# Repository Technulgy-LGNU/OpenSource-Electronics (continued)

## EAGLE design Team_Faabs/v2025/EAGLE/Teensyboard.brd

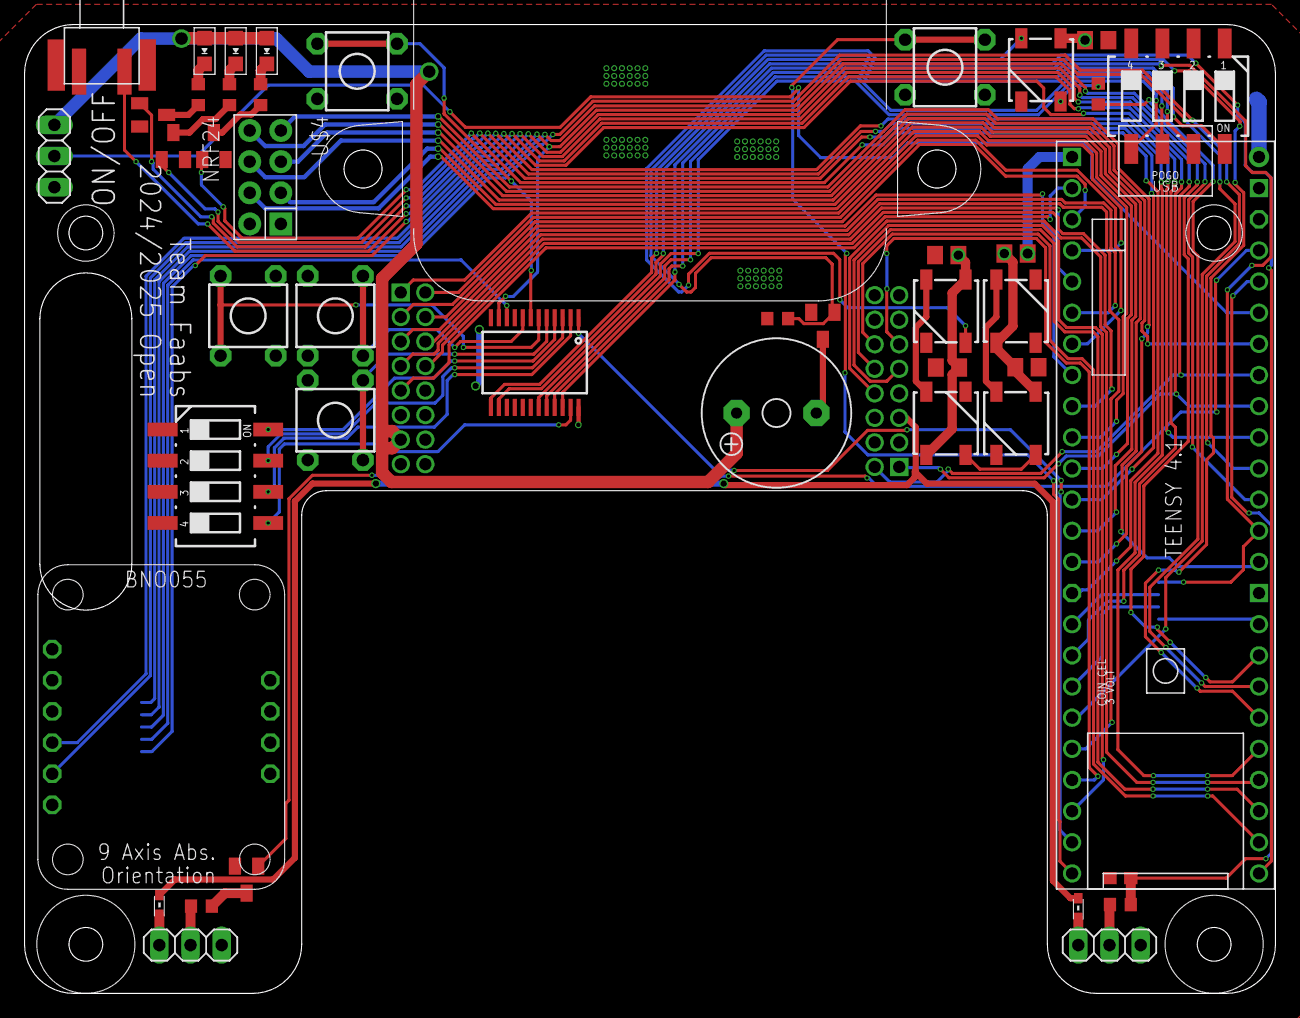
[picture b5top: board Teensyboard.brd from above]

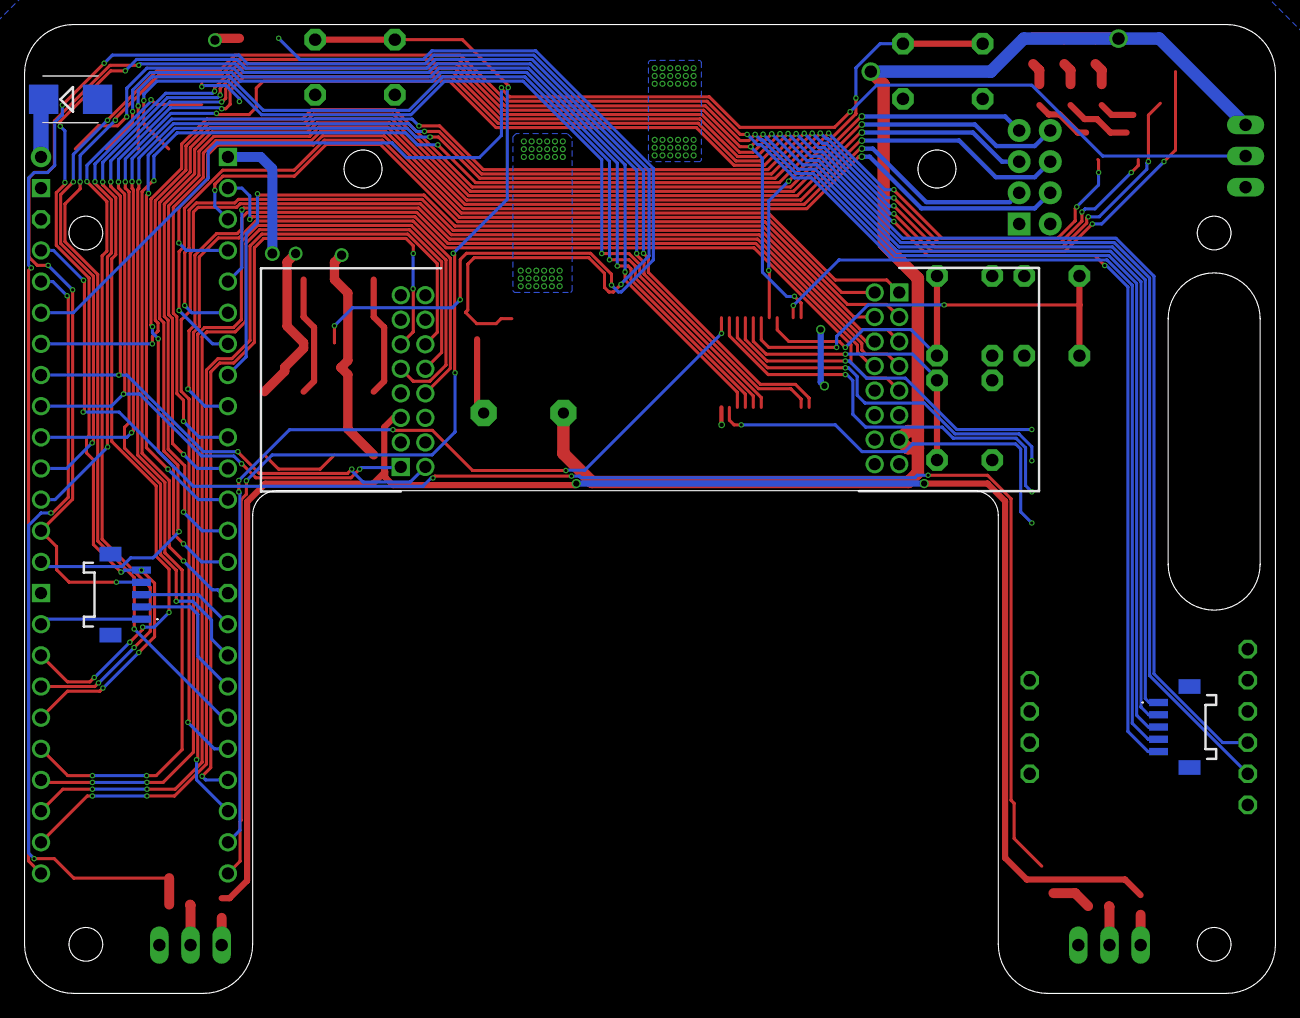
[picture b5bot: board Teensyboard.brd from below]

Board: 2 copper layers, 102.0 x 79.0 mm, 49 parts (5 on the bottom side), 77 nets.

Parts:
C1, C2, C3, C4, C5: 100n; C0805
C6: 1n; C0603
D1: SMB
D6, D7, D8, D9, D10: SPARKFUN-LED_WS2812B
J1, J5: TEENSY_CON_RIGHTANGLED; 208659-1640_SHDRRA16W55P200_2X8_1800X1450X
J3, J4: 5PIN_1MM_CON; 2035600503
JP2, JP3, JP4: 1X03
KNOPF-0, KNOPF-1, KNOPF-2, KNOPF-3, KNOPF-4: KSM611A
L6, L7: 120R; 0603
LED4, LED6, LED8: POWER_DISTRIBUTION_CHIPLED_0805
ON/OFF_SW: TIGERS_KT11
Q1, Q2, Q3, Q4: bss138; TRANSISTOR-SMALL-SIGNAL_SOT23
Q8: BSS138; SOT23
R1, R3, R4: 10k; R0603
R6: 5k; R0603
R13: 470R; R0603
R15: 1k; R0603
R16: 47R; R0603
S1, S2: DEBUG_DILSW; SWITCH-DIL_CTS-219-04
SG1: DEBUG_BUZZER; BUZZER_F/QMX
U$1: MULTIPLEXER_MUX-74HC4067SMD; SPARKFUN_SSOP24
U$2: BNO055
U$3: TEENSY_4.1_WO_EXTRAPINS
U$4: NRF24

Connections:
+3V3: J5.5, L6.1, L7.1
+5V: C1.2, C2.2, C3.2, C4.2, C5.2, D1.A, D6.1, D7.1, D8.1, D9.1, D10.1, J5.15, U$1.24, U$2.VIN, U$4.2
+12V: J1.13, JP4.1, LED4.A, LED6.A, LED8.A, SG1.+
BODEN_0: J3.3, U$3.24-A10/TX6/SCL2
BODEN_1: J4.5, U$3.25-A11/RX6/SDA2
BODEN_2: J3.2, U$3.26-A12/MOSI1
BODEN_3: J4.3, U$3.27-A13/SCK1
BODEN_4: J3.1, U$3.41-A17/MISO1
BODEN_5: J4.1, U$3.40-A16/CS1
BUZZER: Q3.1, R6.1, U$3.33-MCLK2
CE: U$3.9-OUT1C, U$4.3
COMMUNICATION_MOD: JP4.2, U$3.21-A7/RX5/BCLK1
CSN: U$3.8-TX2/IN2, U$4.4
DIP_0: S1.8, U$1.4
DIP_1: S1.7, U$1.3
DIP_2: S1.6, U$1.2
DIP_3: S1.5, U$1.23
DIP_4: S2.8, U$1.22
DIP_5: S2.7, U$1.21
DIP_6: S2.6, U$1.20
DIP_7: S2.5, U$1.19
DRIBBLER_DIR: J5.9, U$3.30-CRX3
DRIBBLER_PWM: J5.11, U$3.29-TX7
DRIVE_EN: J1.9, U$3.0-RX1/CS1/CRX2
D_OUTPUT: U$1.1, U$3.31-CTX3
EN_HV: J5.12, U$3.34-RX8
GND: C1.1, C2.1, C3.1, C4.1, C5.1, C6.2, D6.3, D7.3, D8.3, D9.3, D10.3, J1.11, J5.16, JP3.3, JP4.3, KNOPF-0.B, KNOPF-0.D, KNOPF-1.B, KNOPF-1.D, KNOPF-2.B, KNOPF-2.D, KNOPF-3.B, KNOPF-3.D, KNOPF-4.B, KNOPF-4.D, ON/OFF_SW.2, Q1.2, Q2.2, Q3.2, Q4.2, Q8.2, R6.2, S1.1, S1.2, S1.3, S1.4, S2.1, S2.2, S2.3, S2.4, U$1.12, U$1.15, U$2.GND, U$3.GND1, U$3.GND3, U$3.GND6, U$4.1
I2C_SCL: J5.2, U$2.SCL, U$3.19-A5/SCL0
I2C_SDA: J5.1, U$2.SDA, U$3.18-A4/SDA0
IRQ: U$3.20-A6/TX5/LRCLK1, U$4.8
IR_ADC: C6.1, R15.1, U$3.22-A8/CTX1
IR_LED: Q8.1, U$3.23-A9/CRX1/MCLK1
K0: KNOPF-0.A, KNOPF-0.C, U$3.32-OUT1B
K1: KNOPF-1.A, KNOPF-1.C, U$1.8
K2: KNOPF-2.A, KNOPF-2.C, U$1.7
K3: KNOPF-3.A, KNOPF-3.C, U$1.6
K4: KNOPF-4.A, KNOPF-4.C, U$1.5
LED1: Q1.1, U$3.37-PWM
LED2: Q2.1, U$3.10-CS\MQSR
M_HL_DIR: J1.6, U$3.28-RX7
M_HL_PWM: J1.5, U$3.4-BCLK2
M_HR_DIR: J1.8, U$3.7-RX2/OUT1A
M_HR_PWM: J1.7, U$3.3-LRCLK2
M_VL_DIR: J1.4, U$3.6-OUT1D
M_VL_PWM: J1.1, U$3.2-OUT2
M_VR_DIR: J1.2, U$3.5-IN2
M_VR_PWM: J1.3, U$3.1-TX1/MISO1/CTX2
unnamed: LED8.C, R4.2
unnamed: LED4.C, R1.2
unnamed: LED6.C, R3.2
unnamed: Q1.3, R1.1
unnamed: Q4.3, R4.1
unnamed: Q2.3, R3.1
unnamed: Q3.3, SG1.-
unnamed: D6.4, R13.1
unnamed: D6.2, D7.4
unnamed: D7.2, D8.4
unnamed: D8.2, D9.4
unnamed: D9.2, D10.4
unnamed: JP3.2, R15.2
unnamed: D1.C, U$3.VIN
unnamed: Q8.3, R16.1
unnamed: JP2.2, R16.2
unnamed: JP3.1, L7.2
unnamed: JP2.1, L6.2
NEOPIXELS: R13.2, U$3.39-A15/CS/OUT1A
ON/OFF-BUTTON: ON/OFF_SW.1, U$3.17-A3/TX4/SDA1
S0: J4.4, U$1.10, U$3.16-A2/RX4/SCL1
S1: J4.2, U$1.11, U$3.15-A1/RX3/SPDIF_IN
S2: J3.4, U$1.14, U$3.14-A0/TX3/SPDIF_OUT
S3: J3.5, U$1.13, U$3.38-A14/CS/IN1
SCHUSS_1: J5.8, U$3.36-PWM
SCHUSS_2: J5.10, U$3.35-TX8
SPI_MISO: U$3.12-MISO/MQSL, U$4.7
SPI_MOSI: U$3.11-MOSI/CTX1, U$4.6
SPI_SCK: U$3.13-SCK/LED, U$4.5
T_EN: Q4.1, U$3.3V3-1

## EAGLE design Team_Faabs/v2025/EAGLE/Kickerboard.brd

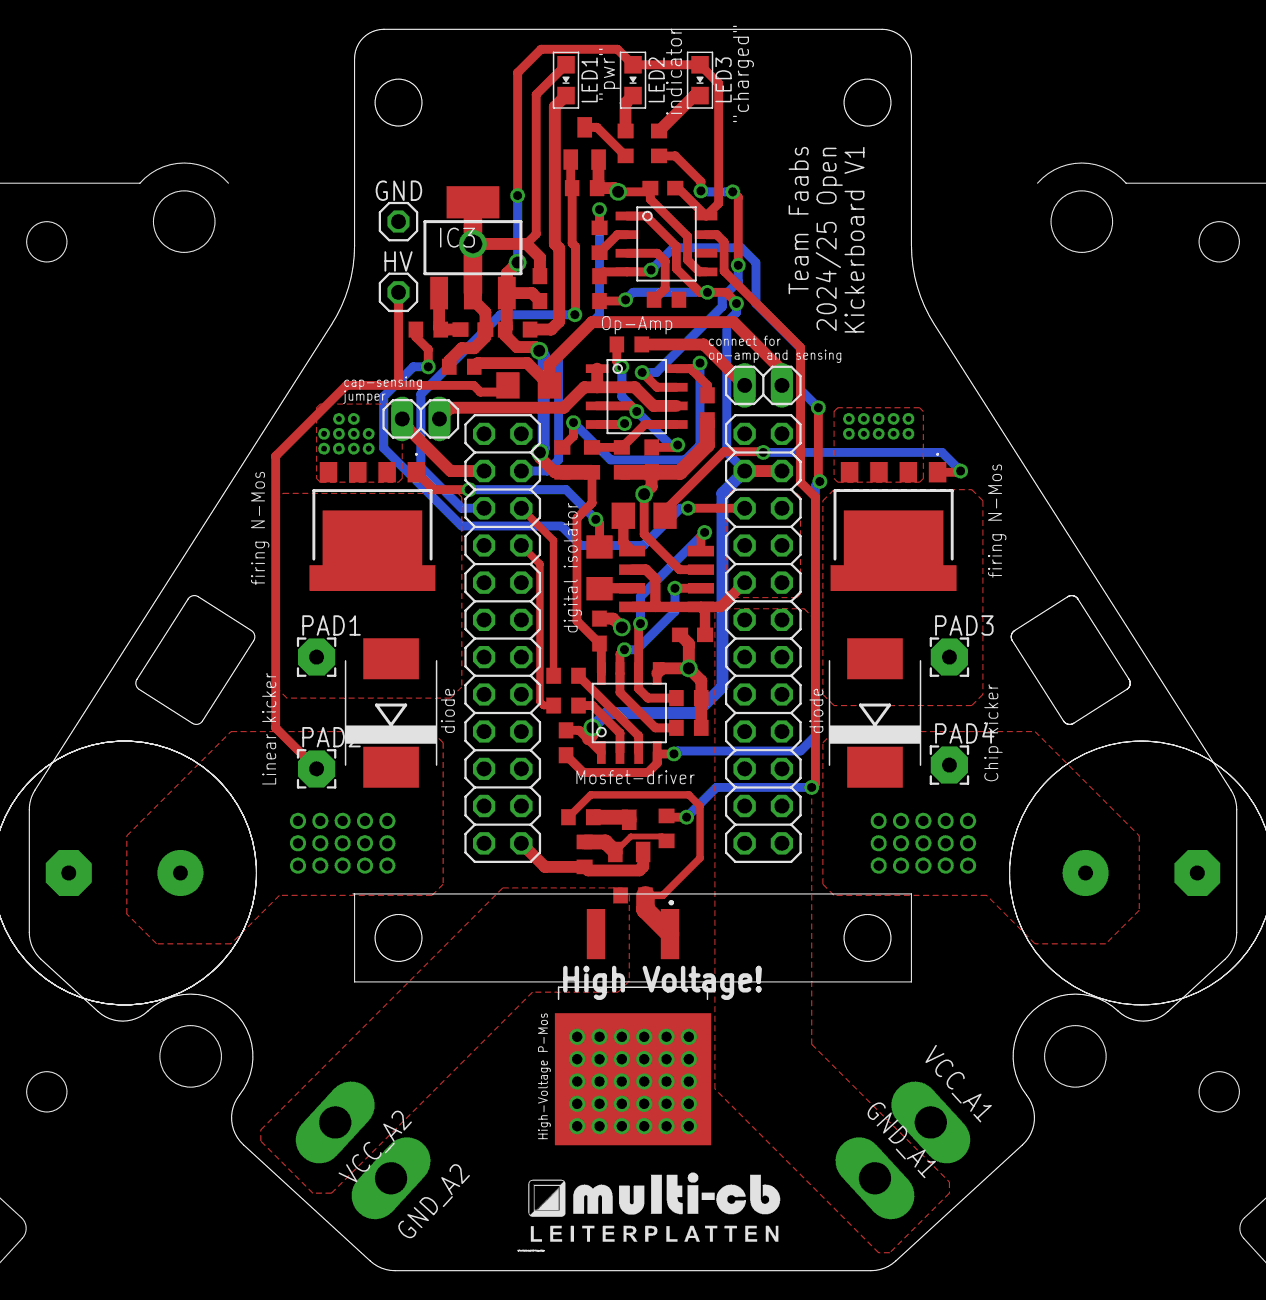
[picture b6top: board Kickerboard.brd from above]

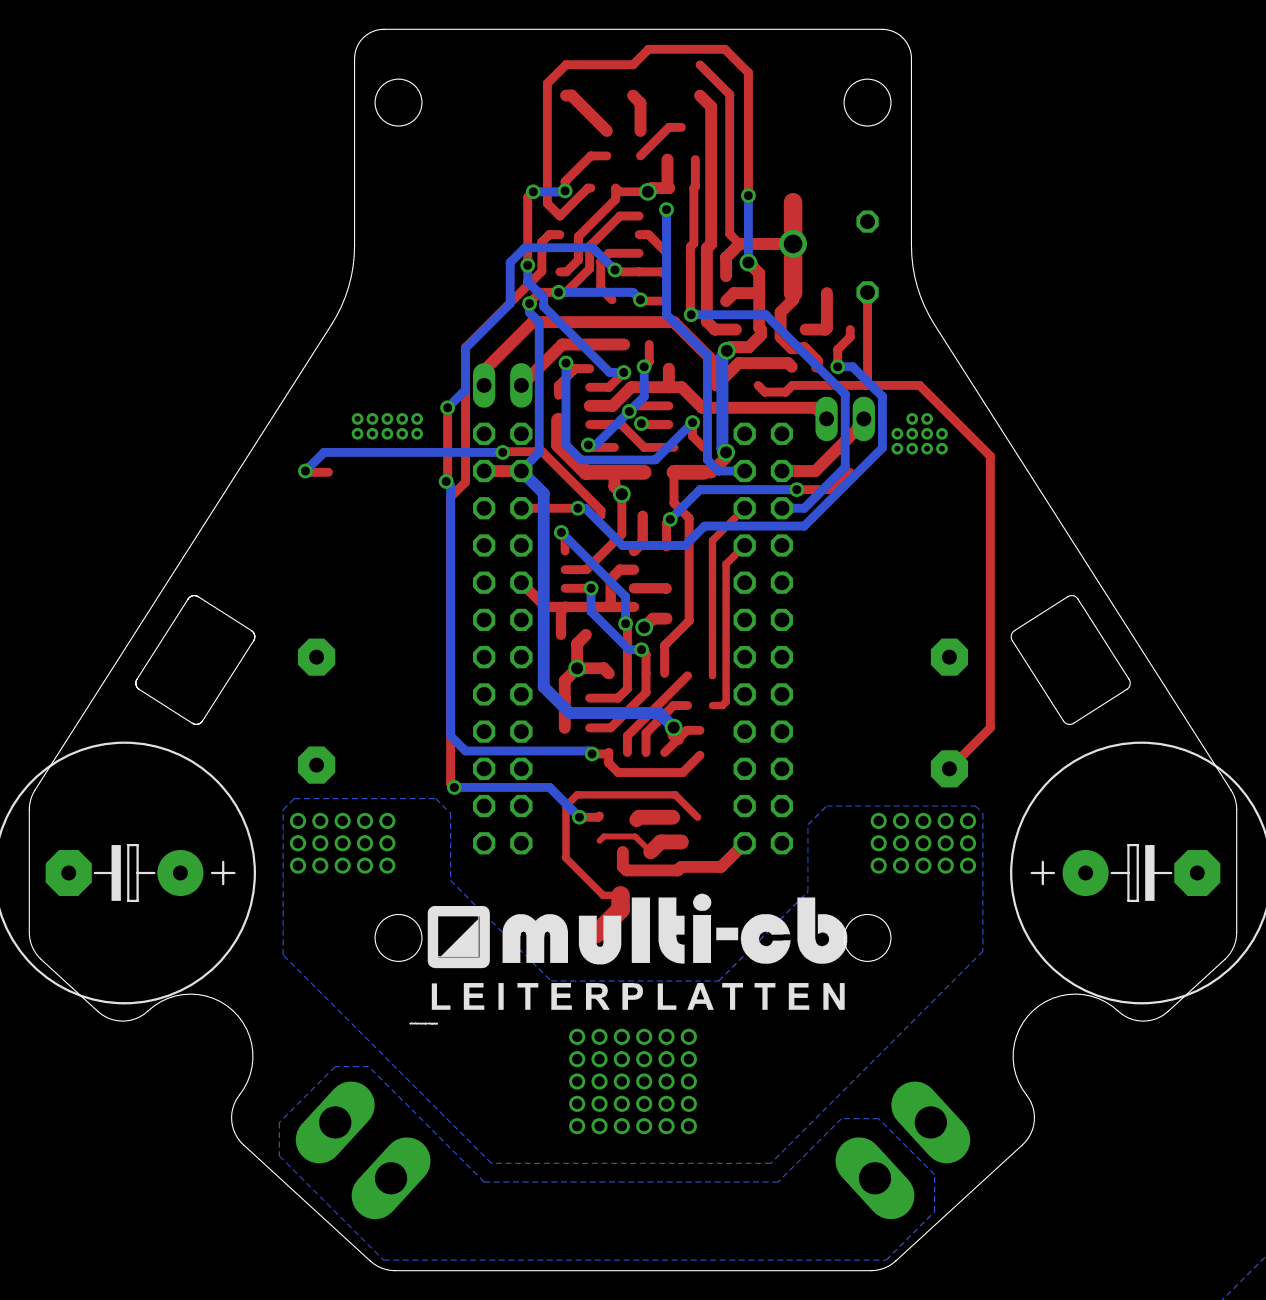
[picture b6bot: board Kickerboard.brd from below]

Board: 2 copper layers, 82.4 x 84.7 mm, 65 parts (3 on the bottom side), 42 nets.

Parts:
C1, C2: 63V, 2200uF; OPEN24_RCL_E7,5-18
C3, C4, C5, C6, C9, C10, C22: 100n; C0603
C24, C25: 10u; C0603
CONNECTOR_MAINPCB1, CONNECTOR_MAINPCB2: 2X12
D1, D2: S10MCH; OPEN24_DIODE_SMC:1
EN_HV-PMOS: SQM120P10; SQM120P10_10M1LGE3_SQM120P10_10M1LGE3
EN_HVSENS: 1X02
GND: 1X01
GND_A1, GND_A2: MOTOR-DRIVER_PPAD
HV: 1X01
HV_SENSED_JP: 1X02
IC1, IC2: TIGERS_SOIC8N
IC3: TIGERS_MCP1790; TIGERS_SOT223
IC4: MCP6002; TIGERS_SOIC8N
L1, L2: 120R, Ferride Bead!!!; R0603
LED1, LED2, LED3: POWER_DISTRIBUTION_CHIPLED_0805
MOSFET-DRIVER: UCC27624QDRQ1; IR_SO08
PAD1, PAD2: LINEAR; TIGERS_2,54/1,0
PAD3, PAD4: CHIP; TIGERS_2,54/1,0
Q1, Q2: PSMN3R3; PSMNR55-40SSHJ_BUK7S1R540HJ
Q3: MMFTN123; TRANSISTOR-SMALL-SIGNAL_SOT23
Q5: bss138; TRANSISTOR-SMALL-SIGNAL_SOT23
R1, R2: 10R; R1206
R3, R4, R5, R12, R14, R16: 1k; R0603
R6, R7, R11, R15, R21: 100R; R0603
R8: 50k; R0603
R9, R10: 10k; R0603
R13: 5k; R0603
R17, R18: 100k; R0603
R19: 10M 0.5%; R1206
R20: 549k; R0603
U$1: MULTICB_LOGOSTANDART; SMALL_STANDARTLOGO_28MM
U$2: MULTICB_LOGOMINI; MINI_LOGO_17MM
VCC_A1, VCC_A2: MOTOR-DRIVER_PPAD

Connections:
+3V3: C5.1, C10.1, C25.1, IC1.8, IC2.8, IC3.3, L2.2, LED2.A, LED3.A, R5.2, R17.1
+12V: C4.1, CONNECTOR_MAINPCB1.15, CONNECTOR_MAINPCB1.16, CONNECTOR_MAINPCB1.17, CONNECTOR_MAINPCB1.18, CONNECTOR_MAINPCB1.19, CONNECTOR_MAINPCB1.20, L1.2, MOSFET-DRIVER.1, MOSFET-DRIVER.6, MOSFET-DRIVER.8
CAP: HV_SENSED_JP.1, IC4.1, IC4.2, IC4.6
CAP-RAW: EN_HVSENS.1, R19.1, R20.2
CAP_RAW: EN_HVSENS.2, R16.2
CHG_LED: IC4.7, R14.1
CHIP: CONNECTOR_MAINPCB2.19, R7.2
EN_HV: IC1.7, R11.1
EN_HV_T: CONNECTOR_MAINPCB2.21, R15.2
GATE_S1: Q1.1, R1.2
GATE_S2: Q2.1, R2.2
GND: C1.-, C2.-, C3.2, C4.2, C5.2, C10.2, C22.2, C24.2, C25.2, CONNECTOR_MAINPCB1.23, CONNECTOR_MAINPCB1.24, CONNECTOR_MAINPCB2.1, CONNECTOR_MAINPCB2.2, CONNECTOR_MAINPCB2.3, CONNECTOR_MAINPCB2.4, CONNECTOR_MAINPCB2.5, CONNECTOR_MAINPCB2.6, CONNECTOR_MAINPCB2.7, CONNECTOR_MAINPCB2.8, CONNECTOR_MAINPCB2.9, CONNECTOR_MAINPCB2.10, CONNECTOR_MAINPCB2.11, CONNECTOR_MAINPCB2.12, CONNECTOR_MAINPCB2.13, CONNECTOR_MAINPCB2.14, GND.1, IC1.5, IC2.5, IC3.2, IC3.4, IC4.4, LED1.A, MOSFET-DRIVER.3, Q1.2, Q1.3, Q1.4, Q2.2, Q2.3, Q2.4, Q3.2, Q5.2, R3.1, R4.1, R10.1, R13.2, R18.2, R20.1
LED1: CONNECTOR_MAINPCB2.20, Q5.1, R13.1
LINEAR: CONNECTOR_MAINPCB2.17, R6.2
MAIN-3V3: C6.1, C9.1, CONNECTOR_MAINPCB1.21, CONNECTOR_MAINPCB1.22, IC1.1, IC2.1
unnamed: MOSFET-DRIVER.5, R2.1
unnamed: MOSFET-DRIVER.7, R1.1
unnamed: D2.A, PAD3.1, Q2.5, Q2.6
unnamed: IC2.2, R6.1
unnamed: IC2.3, R7.1
unnamed: EN_HV-PMOS.GATE, R8.2, R9.1
unnamed: Q3.3, R8.1
unnamed: C24.1, IC3.1, L1.1
unnamed: IC1.2, R15.1
unnamed: D1.A, PAD1.1, Q1.5, Q1.6
unnamed: Q3.1, R10.2, R11.2
unnamed: IC1.3, R21.1
unnamed: LED2.C, R12.2
unnamed: Q5.3, R12.1
unnamed: LED1.C, R5.1
unnamed: CONNECTOR_MAINPCB2.22, HV_SENSED_JP.2
unnamed: LED3.C, R14.2
unnamed: C6.2, C9.2, IC1.4, IC2.4
unnamed: C3.1, IC4.3, R16.1
unnamed: IC4.5, R17.2, R18.1
unnamed: GND_A2.P$1, VCC_A1.P$1
unnamed: C22.1, IC4.8, L2.1
SCHUSS1-: IC2.7, MOSFET-DRIVER.2, R4.2
SCHUSS2-: IC2.6, MOSFET-DRIVER.4, R3.2
VCC: CONNECTOR_MAINPCB1.1, CONNECTOR_MAINPCB1.2, CONNECTOR_MAINPCB1.3, CONNECTOR_MAINPCB1.4, CONNECTOR_MAINPCB1.5, CONNECTOR_MAINPCB1.6, CONNECTOR_MAINPCB1.7, CONNECTOR_MAINPCB1.8, CONNECTOR_MAINPCB1.9, CONNECTOR_MAINPCB1.10, CONNECTOR_MAINPCB1.11, CONNECTOR_MAINPCB1.12, CONNECTOR_MAINPCB1.13, CONNECTOR_MAINPCB1.14, GND_A1.P$1
VCC_HV: C1.+, C2.+, D1.C, D2.C, EN_HV-PMOS.DRAIN, HV.1, PAD2.1, PAD4.1, R19.2
VCC_HV_BAT: EN_HV-PMOS.SOURCE, R9.2, VCC_A2.P$1

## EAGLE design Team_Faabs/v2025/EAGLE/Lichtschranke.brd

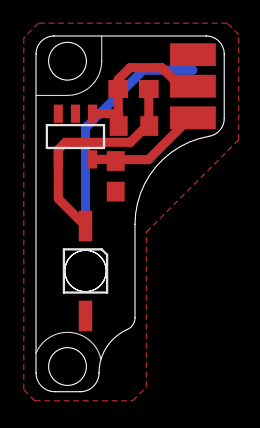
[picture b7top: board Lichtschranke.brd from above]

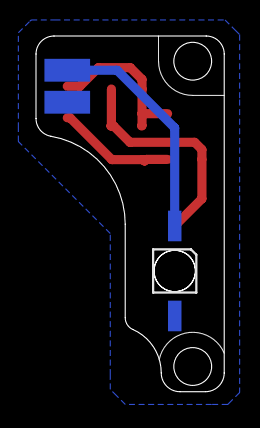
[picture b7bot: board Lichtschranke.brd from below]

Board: 2 copper layers, 10.5 x 19.8 mm, 11 parts (3 on the bottom side), 6 nets.

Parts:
C1: 10p; C0603
C2: 10u; C0603
D2: VSMB2000X01; LED-GULLR
D3: TEMD1000; LED-GULLR
IC1: OPA320; SOT23-5
PAD1, PAD2, PAD3, PAD4, PAD5: SMD1,27-2,54
R1: 1M; R0603

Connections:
+3V3: C2.2, IC1.5, PAD2.1
GND: C2.1, D3.A, IC1.2, IC1.3, PAD3.1
GNDA: D2.C, PAD4.1
IR-ADC_OUT: C1.2, IC1.1, PAD1.1, R1.2
unnamed: C1.1, D3.C, IC1.4, R1.1
VCC: D2.A, PAD5.1

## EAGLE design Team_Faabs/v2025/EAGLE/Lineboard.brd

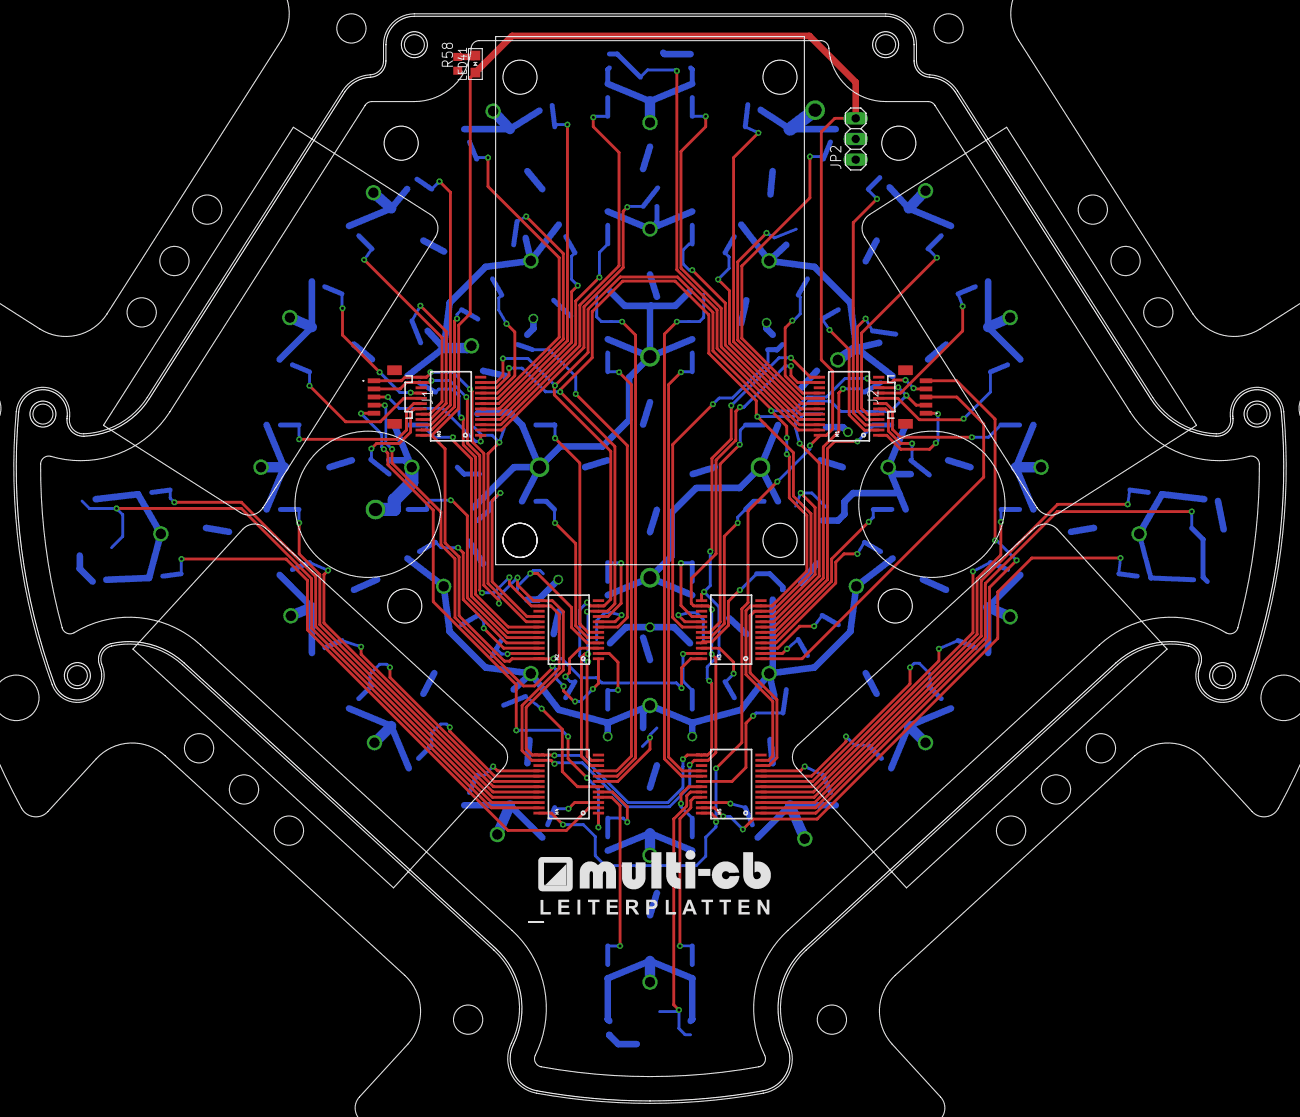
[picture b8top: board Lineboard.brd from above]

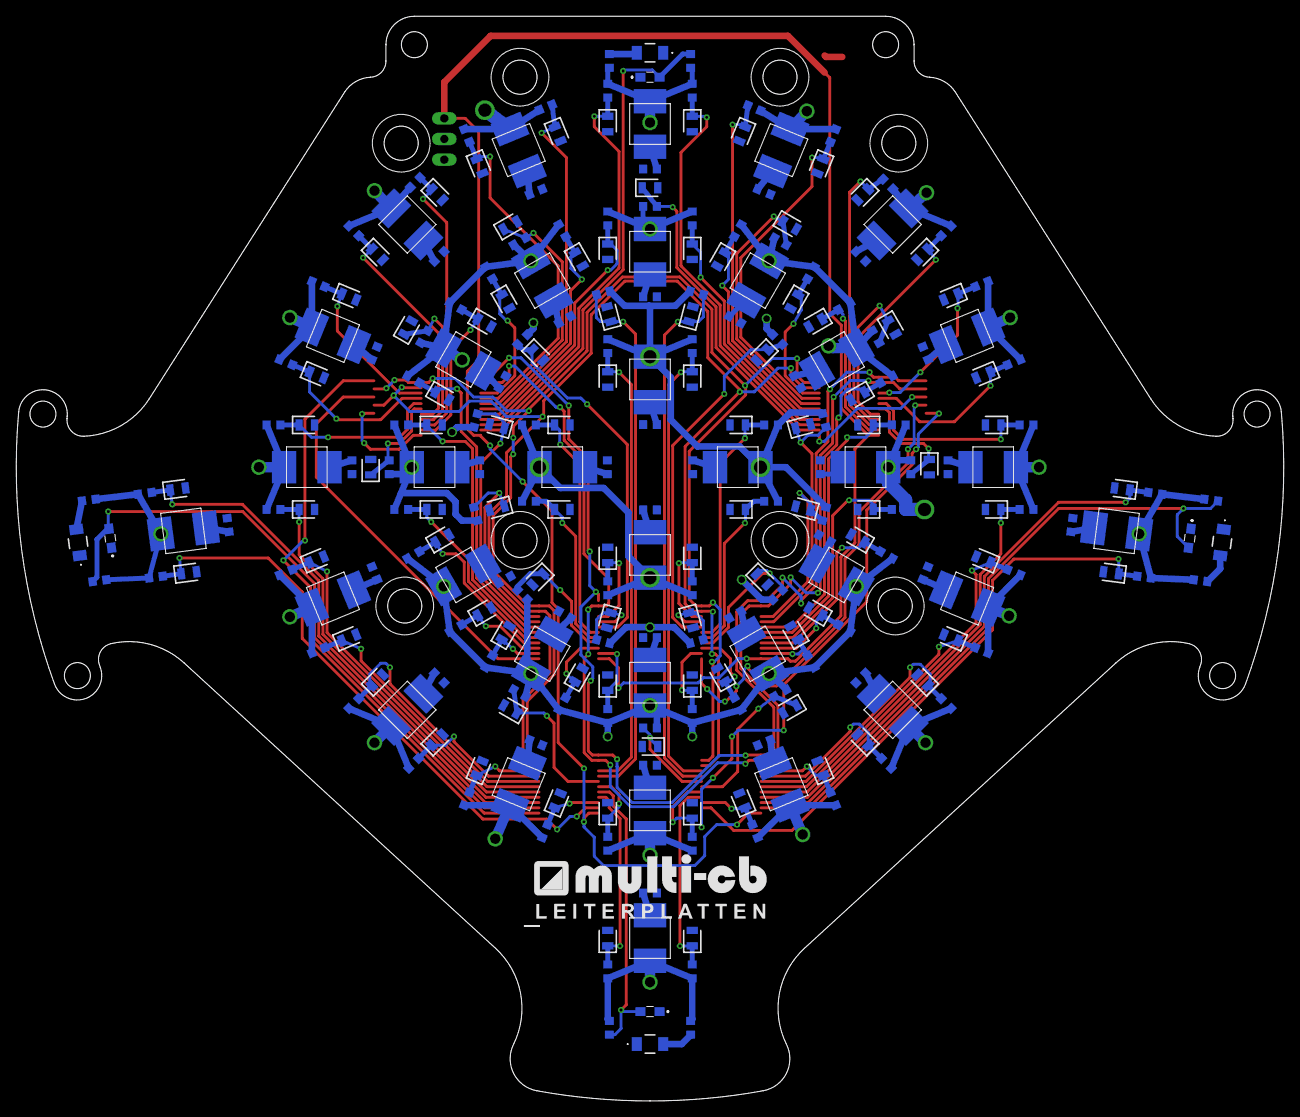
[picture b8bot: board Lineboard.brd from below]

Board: 2 copper layers, 156.0 x 133.5 mm, 283 parts (271 on the bottom side), 149 nets.

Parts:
J1, J2: 5PIN_1MM_CON; 2035600503
JP2: 1X03
LED01, LED02, LED03, LED04, LED11, LED12, LED13, LED14, LED15, LED16, LED17, LED18, LED19, LED21, LED22, LED23, LED24, LED25, LED26, LED27, LED28, LED29, LED31, LED32, LED33, LED110, LED111, LED112, LED210, LED211, LED212, LED213, LED214, LED215, LED216: RND135-00056LEDD; LED
LED5, LED06, LED09, LED10: SFH_4656-Z; SFH4656Z
LED41: POWER_DISTRIBUTION_CHIPLED_0805
M0, M1, M2, M3, M4, M5: MULTIPLEXER_MUX-74HC4067SMD; SPARKFUN_SSOP24
Q1, Q2, Q5, Q6: AP2012P3C-P22; AP2012P3CP22
R01, R02, R03, R04, R05, R06, R07, R11, R12, R13, R14, R15, R16, R17, R18, R19, R21, R22, R23, R24, R25, R26, R27, R28, R29, R110, R111, R112, R210, R211, R212, R213, R214, R215, R216: 120R; R0603
R08, R32, R34, R42: 10k; R0603
R09, R33, R35, R43, R58: 1k; R0603
RP01, RP02, RP03, RP04, RP05, RP06, RP07, RP08, RP11, RP12, RP13, RP14, RP15, RP16, RP17, RP18, RP19, RP21, RP22, RP23, RP24, RP25, RP26, RP27, RP28, RP29, RP31, RP32, RP33, RP34, RP35, RP36, RP41, RP42, RP43, RP44, RP45, RP46, RP47, RP48, RP49, RP51, RP52, RP53, RP54, RP55, RP56, RP57, RP59, RP110, RP111, RP112, RP113, RP114, RP115, RP116, RP117, RP118, RP119, RP120, RP121, RP122, RP123, RP124, RP210, RP211, RP212, RP213, RP214, RP215, RP216, RP217, RP218, RP219, RP220, RP221, RP222, RP223, RP224, RP225, RP226, RP227, RP228, RP229, RP230, RP231, RP232, RP410, RP411, RP412, RP510, RP511: 3k3; R0603
SFH01, SFH02, SFH03, SFH04, SFH05, SFH06, SFH07, SFH08, SFH11, SFH12, SFH13, SFH14, SFH15, SFH16, SFH17, SFH18, SFH19, SFH21, SFH22, SFH23, SFH24, SFH25, SFH26, SFH27, SFH28, SFH29, SFH31, SFH32, SFH33, SFH34, SFH35, SFH36, SFH41, SFH42, SFH43, SFH44, SFH45, SFH46, SFH47, SFH48, SFH49, SFH51, SFH52, SFH53, SFH54, SFH55, SFH56, SFH57, SFH59, SFH110, SFH111, SFH112, SFH113, SFH114, SFH115, SFH116, SFH117, SFH118, SFH119, SFH120, SFH121, SFH122, SFH123, SFH124, SFH210, SFH211, SFH212, SFH213, SFH214, SFH215, SFH216, SFH217, SFH218, SFH219, SFH220, SFH221, SFH222, SFH223, SFH224, SFH225, SFH226, SFH227, SFH228, SFH229, SFH230, SFH231, SFH232, SFH410, SFH411, SFH412, SFH510, SFH511: LEDC2012X89N
U$1, U$5: MULTICB_LOGOSTANDART; SMALL_STANDARTLOGO_28MM

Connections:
01: M5.16, RP01.2, SFH01.1
02: M4.9, RP02.2, SFH02.1
03: M3.19, RP03.2, SFH03.1
04: M3.20, RP04.2, SFH04.1
05: M2.9, RP05.2, SFH05.1
06: M3.16, RP06.2, SFH06.1
07: M2.6, RP07.2, SFH07.1
08: M2.5, RP08.2, SFH08.1
11: M3.5, RP11.2, SFH11.1
12: M3.6, RP12.2, SFH12.1
13: M3.7, RP13.2, SFH13.1
14: M1.2, RP14.2, SFH14.1
15: M1.16, RP15.2, SFH15.1
16: M1.20, RP16.2, SFH16.1
17: M1.21, RP17.2, SFH17.1
18: M0.4, RP18.2, SFH18.1
19: M0.5, RP19.2, SFH19.1
21: M5.4, RP21.2, SFH21.1
22: M1.7, RP22.2, SFH22.1
23: M1.8, RP23.2, SFH23.1
24: M1.9, RP24.2, SFH24.1
25: M1.5, RP25.2, SFH25.1
26: M1.3, RP26.2, SFH26.1
27: M1.17, RP27.2, SFH27.1
28: M1.19, RP28.2, SFH28.1
29: M1.22, RP29.2, SFH29.1
31: M5.23, RP31.2, SFH31.1
32: M5.3, RP32.2, SFH32.1
33: M4.22, RP33.2, SFH33.1
34: M4.2, RP34.2, SFH34.1
35: M4.4, RP35.2, SFH35.1
36: M5.21, RP36.2, SFH36.1
41: M3.8, RP41.2, SFH41.1
42: M3.18, RP42.2, SFH42.1
43: M5.17, RP43.2, SFH43.1
44: M4.8, RP44.2, SFH44.1
45: M2.7, RP45.2, SFH45.1
46: M2.17, RP46.2, SFH46.1
47: M2.16, RP47.2, SFH47.1
48: M2.4, RP48.2, SFH48.1
49: M2.8, RP49.2, SFH49.1
51: M1.6, RP51.2, SFH51.1
52: M1.4, RP52.2, SFH52.1
53: M1.18, RP53.2, SFH53.1
54: M0.2, RP54.2, SFH54.1
55: M0.7, RP55.2, SFH55.1
56: M0.21, RP56.2, SFH56.1
57: M0.19, RP57.2, SFH57.1
59: M4.6, RP59.2, SFH59.1
110: M0.9, RP110.2, SFH110.1
111: M0.23, RP111.2, SFH111.1
112: M2.18, RP112.2, SFH112.1
113: M2.19, RP113.2, SFH113.1
114: M2.20, RP114.2, SFH114.1
115: M2.21, RP115.2, SFH115.1
116: M2.22, RP116.2, SFH116.1
117: M2.23, RP117.2, SFH117.1
118: M2.3, RP118.2, SFH118.1
119: M2.2, RP119.2, SFH119.1
120: M3.23, RP120.2, SFH120.1
121: M3.22, RP121.2, SFH121.1
122: M3.2, RP122.2, SFH122.1
123: M3.3, RP123.2, SFH123.1
124: M3.4, RP124.2, SFH124.1
210: M0.3, RP210.2, SFH210.1
211: M0.6, RP211.2, SFH211.1
212: M0.8, RP212.2, SFH212.1
213: M0.22, RP213.2, SFH213.1
214: M0.20, RP214.2, SFH214.1
215: M0.16, RP215.2, SFH215.1
216: M0.17, RP216.2, SFH216.1
217: M0.18, RP217.2, SFH217.1
218: M4.21, RP218.2, SFH218.1
219: M4.20, RP219.2, SFH219.1
220: M4.19, RP220.2, SFH220.1
221: M4.18, RP221.2, SFH221.1
222: M4.17, RP222.2, SFH222.1
223: M4.16, RP223.2, SFH223.1
224: M4.3, RP224.2, SFH224.1
225: M4.5, RP225.2, SFH225.1
226: M5.19, RP226.2, SFH226.1
227: M5.22, RP227.2, SFH227.1
228: M5.9, RP228.2, SFH228.1
229: M5.8, RP229.2, SFH229.1
230: M5.7, RP230.2, SFH230.1
231: M5.6, RP231.2, SFH231.1
232: M5.5, RP232.2, SFH232.1
410: M3.17, RP410.2, SFH410.1
411: M3.21, RP411.2, SFH411.1
412: M3.9, RP412.2, SFH412.1
510: M4.7, RP510.2, SFH510.1
511: M5.18, RP511.2, SFH511.1
+3V3: JP2.2, LED5.1, LED06.1, LED09.1, LED10.1, Q1.1, Q2.1, Q5.1, Q6.1, R01.2, R02.2, R03.2, R04.2, R05.2, R06.2, R07.2, R11.2, R12.2, R13.2, R14.2, R15.2, R16.2, R17.2, R18.2, R19.2, R21.2, R22.2, R23.2, R24.2, R25.2, R26.2, R27.2, R28.2, R29.2, R110.2, R111.2, R112.2, R210.2, R211.2, R212.2, R213.2, R214.2, R215.2, R216.2, SFH01.2, SFH02.2, SFH03.2, SFH04.2, SFH05.2, SFH06.2, SFH07.2, SFH08.2, SFH11.2, SFH12.2, SFH13.2, SFH14.2, SFH15.2, SFH16.2, SFH17.2, SFH18.2, SFH19.2, SFH21.2, SFH22.2, SFH23.2, SFH24.2, SFH25.2, SFH26.2, SFH27.2, SFH28.2, SFH29.2, SFH31.2, SFH32.2, SFH33.2, SFH34.2, SFH35.2, SFH36.2, SFH41.2, SFH42.2, SFH43.2, SFH44.2, SFH45.2, SFH46.2, SFH47.2, SFH48.2, SFH49.2, SFH51.2, SFH52.2, SFH53.2, SFH54.2, SFH55.2, SFH56.2, SFH57.2, SFH59.2, SFH110.2, SFH111.2, SFH112.2, SFH113.2, SFH114.2, SFH115.2, SFH116.2, SFH117.2, SFH118.2, SFH119.2, SFH120.2, SFH121.2, SFH122.2, SFH123.2, SFH124.2, SFH210.2, SFH211.2, SFH212.2, SFH213.2, SFH214.2, SFH215.2, SFH216.2, SFH217.2, SFH218.2, SFH219.2, SFH220.2, SFH221.2, SFH222.2, SFH223.2, SFH224.2, SFH225.2, SFH226.2, SFH227.2, SFH228.2, SFH229.2, SFH230.2, SFH231.2, SFH232.2, SFH410.2, SFH411.2, SFH412.2, SFH510.2, SFH511.2
+5V: JP2.3, LED41.A, M0.24, M1.24, M2.24, M3.24, M4.24, M5.24
GND: JP2.1, LED01.123, LED02.123, LED03.123, LED04.123, LED11.123, LED12.123, LED13.123, LED14.123, LED15.123, LED16.123, LED17.123, LED18.123, LED19.123, LED21.123, LED22.123, LED23.123, LED24.123, LED25.123, LED26.123, LED27.123, LED28.123, LED29.123, LED31.123, LED32.123, LED33.123, LED110.123, LED111.123, LED112.123, LED210.123, LED211.123, LED212.123, LED213.123, LED214.123, LED215.123, LED216.123, M0.12, M0.15, M1.12, M1.15, M2.12, M2.15, M3.12, M3.15, M4.12, M4.15, M5.12, M5.15, R08.1, R09.1, R32.1, R33.1, R34.1, R35.1, R42.1, R43.1, R58.1, RP01.1, RP02.1, RP03.1, RP04.1, RP05.1, RP06.1, RP07.1, RP08.1, RP11.1, RP12.1, RP13.1, RP14.1, RP15.1, RP16.1, RP17.1, RP18.1, RP19.1, RP21.1, RP22.1, RP23.1, RP24.1, RP25.1, RP26.1, RP27.1, RP28.1, RP29.1, RP31.1, RP32.1, RP33.1, RP34.1, RP35.1, RP36.1, RP41.1, RP42.1, RP43.1, RP44.1, RP45.1, RP46.1, RP47.1, RP48.1, RP49.1, RP51.1, RP52.1, RP53.1, RP54.1, RP55.1, RP56.1, RP57.1, RP59.1, RP110.1, RP111.1, RP112.1, RP113.1, RP114.1, RP115.1, RP116.1, RP117.1, RP118.1, RP119.1, RP120.1, RP121.1, RP122.1, RP123.1, RP124.1, RP210.1, RP211.1, RP212.1, RP213.1, RP214.1, RP215.1, RP216.1, RP217.1, RP218.1, RP219.1, RP220.1, RP221.1, RP222.1, RP223.1, RP224.1, RP225.1, RP226.1, RP227.1, RP228.1, RP229.1, RP230.1, RP231.1, RP232.1, RP410.1, RP411.1, RP412.1, RP510.1, RP511.1
IR1: M1.23, Q2.2, R42.2
IR2: M5.20, Q1.2, R08.2
IR3: M5.2, Q5.2, R32.2
IR4: M4.23, Q6.2, R34.2
unnamed: LED11.456, R11.1
unnamed: LED12.456, R12.1
unnamed: LED13.456, R13.1
unnamed: LED14.456, R14.1
unnamed: LED15.456, R15.1
unnamed: LED16.456, R16.1
unnamed: LED17.456, R17.1
unnamed: LED18.456, R18.1
unnamed: LED19.456, R19.1
unnamed: LED110.456, R110.1
unnamed: LED111.456, R111.1
unnamed: LED112.456, R112.1
unnamed: LED21.456, R21.1
unnamed: LED22.456, R22.1
unnamed: LED23.456, R23.1
unnamed: LED24.456, R24.1
unnamed: LED25.456, R25.1
unnamed: LED26.456, R26.1
unnamed: LED27.456, R27.1
unnamed: LED28.456, R28.1
unnamed: LED01.456, R01.1
unnamed: LED02.456, R02.1
unnamed: LED03.456, R03.1
unnamed: LED04.456, R04.1
unnamed: LED29.456, R29.1
unnamed: LED210.456, R210.1
unnamed: LED211.456, R211.1
unnamed: LED212.456, R212.1
unnamed: LED213.456, R213.1
unnamed: LED214.456, R214.1
unnamed: LED215.456, R215.1
unnamed: LED216.456, R216.1
unnamed: LED31.456, R05.1
unnamed: LED32.456, R06.1
unnamed: LED33.456, R07.1
unnamed: LED06.2, R09.2
unnamed: LED5.2, R43.2
unnamed: LED09.2, R33.2
unnamed: LED10.2, R35.2
unnamed: LED41.C, R58.2
S0: J2.2, M0.10, M1.10, M2.10, M3.10, M4.10, M5.10
S1: J2.4, M0.11, M1.11, M2.11, M3.11, M4.11, M5.11
S2: J1.2, M0.14, M1.14, M2.14, M3.14, M4.14, M5.14
S3: J1.1, M0.13, M1.13, M2.13, M3.13, M4.13, M5.13
SIGNAL_OUT_0: J1.3, M0.1
SIGNAL_OUT_1: J2.1, M1.1
SIGNAL_OUT_2: J1.4, M2.1
SIGNAL_OUT_3: J2.3, M3.1
SIGNAL_OUT_4: J1.5, M4.1
SIGNAL_OUT_5: J2.5, M5.1

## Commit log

2025-07-10 Team Faabs OpenSource release 2025
2025-07-10 changed folder structure
2025-07-10 Add OBG-Electronics.png via upload
2025-07-10 fixed ReadMe.md
2025-07-13 OpenSource publication of our electronics!
